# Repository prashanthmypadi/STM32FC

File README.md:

# STM32FC
STM32F1 based Flight Controller with 9dof IMU (LSM9DS1) and serial 32M Flash.
Upto 4 servo outputs.
PPM RC input
Connectors for external UART and I2C modules.
Battery Voltage monitoring.

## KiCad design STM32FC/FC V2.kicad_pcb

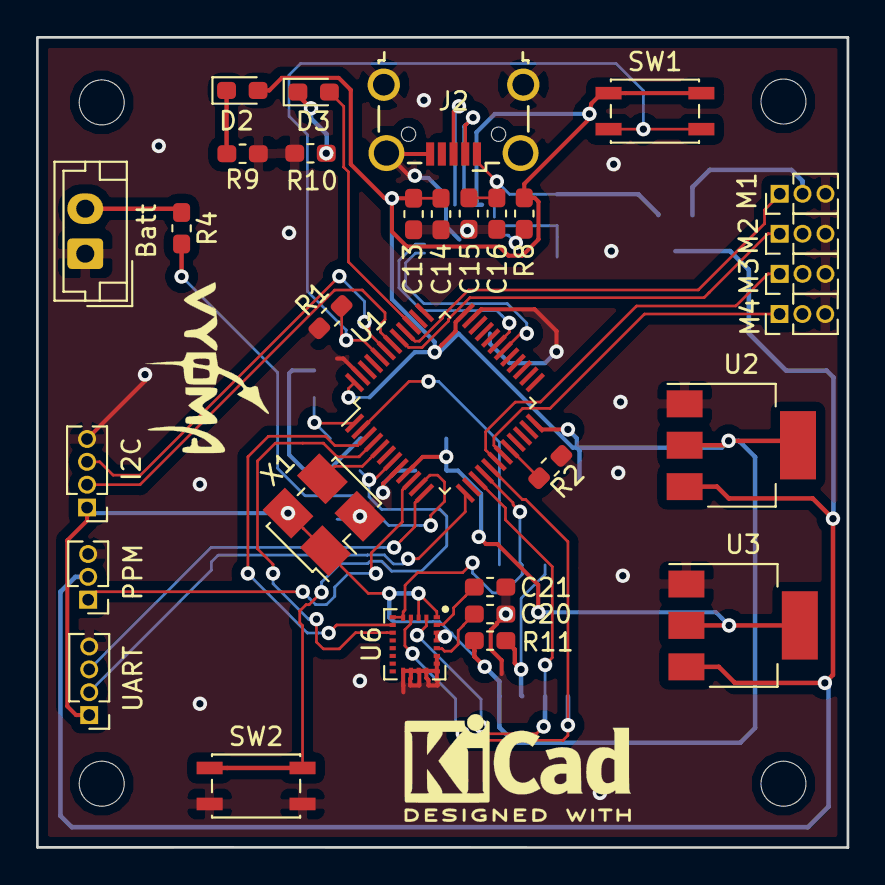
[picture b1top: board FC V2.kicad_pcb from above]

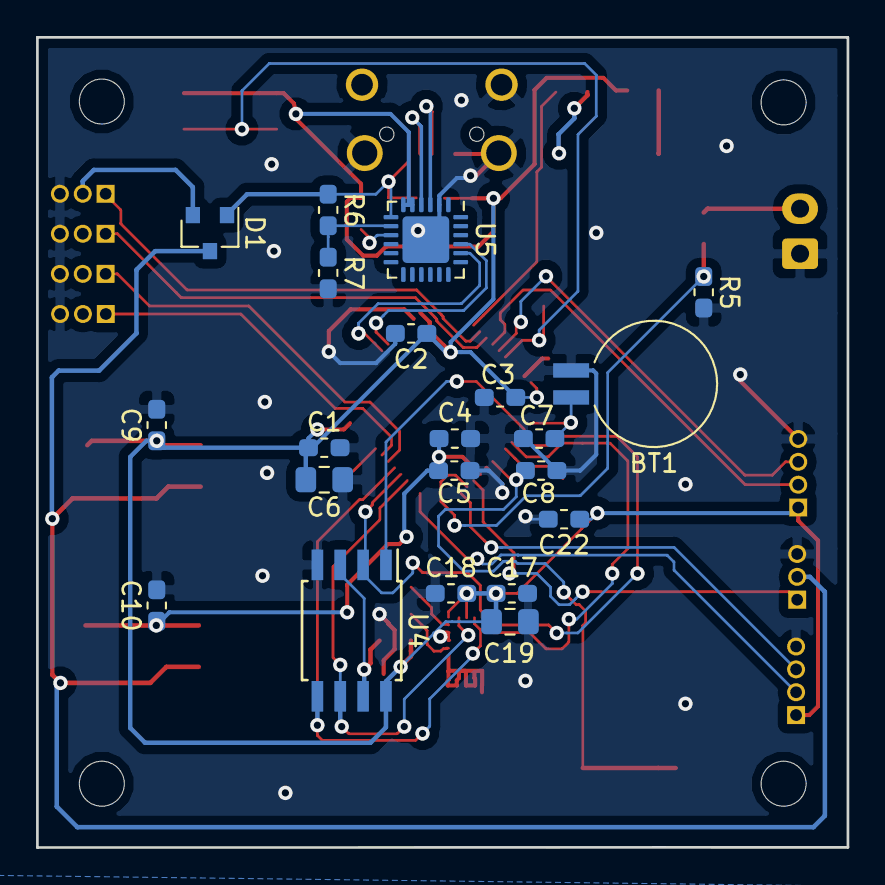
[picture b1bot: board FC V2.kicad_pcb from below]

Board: 2 copper layers, 45.0 x 45.0 mm, 56 parts (21 on the bottom side), 40 nets.

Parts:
BT1: MS621F; BatteryHolder_Seiko_MS621F
C1, C2, C3, C4, C7, C8, C13, C15, C17, C18, C21: 100n; C_0603_1608Metric_Pad1.05x0.95mm_HandSolder
C5, C9, C10: 1u; C_0603_1608Metric_Pad1.05x0.95mm_HandSolder
C6, C19: 10u; C_0805_2012Metric_Pad1.15x1.40mm_HandSolder
C14, C16: 4.7u; C_0603_1608Metric_Pad1.05x0.95mm_HandSolder
C20, C22: 10n; C_0603_1608Metric_Pad1.05x0.95mm_HandSolder
D1: BAT54C; SOT-23
D2: POWER; LED_0603_1608Metric_Pad1.05x0.95mm_HandSolder
D3: LD1; LED_0603_1608Metric_Pad1.05x0.95mm_HandSolder
H1, H2, H3, H4: MountingHole; MountingHole_2.5mm
J1: PPM; PinHeader_1x03_P1.27mm_Vertical
J2: USB; USB_Micro-B_Wuerth_629105150521_CircularHoles
J3: Batt; JST_EH_B02B-EH-A_1x02_P2.50mm_Vertical
J4: M1; PinHeader_1x03_P1.27mm_Vertical
J5: M2; PinHeader_1x03_P1.27mm_Vertical
J6: M3; PinHeader_1x03_P1.27mm_Vertical
J7: M4; PinHeader_1x03_P1.27mm_Vertical
J8: UART; PinHeader_1x04_P1.27mm_Vertical
J9: I2C; PinHeader_1x04_P1.27mm_Vertical
R1, R2, R5: 10k; R_0603_1608Metric_Pad1.05x0.95mm_HandSolder
R4: 41.2k; R_0603_1608Metric_Pad1.05x0.95mm_HandSolder
R6: 22.1k; R_0603_1608Metric_Pad1.05x0.95mm_HandSolder
R7: 47.5k; R_0603_1608Metric_Pad1.05x0.95mm_HandSolder
R8, R11: 1k; R_0603_1608Metric_Pad1.05x0.95mm_HandSolder
R9, R10: 330; R_0603_1608Metric_Pad1.05x0.95mm_HandSolder
SW1: BOOT; SW_SPST_EVQP2
SW2: RESET; SW_SPST_EVQP2
U1: STM32F103C8T6; LQFP-48_7x7mm_P0.5mm
U2, U3: AMS1117-3.3; SOT-223-3_TabPin2
U4: M25PX32; SOIJ-8_5.3x5.3mm_P1.27mm
U5: CP2102N; QFN-24-1EP_4x4mm_P0.5mm_EP2.6x2.6mm
U6: LSM9DS1; LGA-24L_3x3.5mm_P0.43mm
X1: SG-5032CA; Oscillator_SMD_SeikoEpson_SG8002LB-4Pin_5.0x3.2mm_HandSolde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

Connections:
+3.3VA: C4.1, C5.1, C10.1, U1.9, U3.2
+3V3: C1.1, C2.1, C3.1, C6.1, C9.1, C13.1, C14.1, C17.1, C18.1, C19.1, C22.1, D2.2, J8.1, J9.1, R8.1, R11.1, SW1.1, U1.24, U1.36, U1.48, U2.2, U4.8, U5.5, U5.6, U6.1, U6.3, U6.22, U6.23, X1.1, X1.4
+BATT: BT1.1, C7.1, U1.1
BOOT: R1.1, SW1.2, U1.44
CS0#: U1.2, U4.1
CS1#: U1.3, U6.7
CS2#: U1.4, U6.8
D+: J2.3, U5.3
D-: J2.2, U5.4
GNDA: BT1.2, C1.2, C2.2, C3.2, C4.2, C5.2, C6.2, C7.2, C8.2, C9.2, C10.2, C13.2, C14.2, C15.2, C16.2, C17.2, C18.2, C19.2, C20.2, C21.2, C22.2, J1.3, J2.5, J2.6, J3.1, J4.3, J5.3, J6.3, J7.3, J8.4, J9.4, R1.2, R2.2, R5.2, R7.2, R9.1, R10.1, SW2.2, U1.8, U1.23, U1.35, U1.47, U2.1, U3.1, U4.4, U5.2, U5.25, U6.14, U6.15, U6.16, U6.17, U6.18, U6.19, U6.20, X1.2
LED1: D3.2, U1.39
MISO: U1.16, U4.2, U6.5, U6.6
MOSI: U1.17, U4.5, U6.4
unnamed: C20.1, U6.21
unnamed: C21.1, U6.24
unnamed: D2.1, R9.2
unnamed: D3.1, R10.2
unnamed: R2.1, U1.20
unnamed: R8.2, U5.9
unnamed: R11.2, U4.3, U4.7
O1: J4.1, U1.40
O2: J5.1, U1.41
O3: J6.1, U1.18
O4: J7.1, U1.19
OSC_IN: U1.5, X1.3
PPM_In: J1.1, U1.10
RST: C8.1, SW2.1, U1.7
Rx: U1.31, U5.21
Rx1: J8.2, U1.13
SCK: U1.15, U4.6, U6.2
SCL: J9.2, U1.42
SDA: J9.3, U1.43
Tx: U1.30, U5.20
Tx1: J8.3, U1.12
V1: D1.2, J4.2
VBus: R6.2, R7.1, U5.8
VMAIN: J3.2, R4.1
VRegIn: C15.1, C16.1, D1.1, J2.1, R6.1, U5.7
VSENSE: R4.2, R5.1, U1.11
Vin: D1.3, J1.2, U2.3, U3.3
